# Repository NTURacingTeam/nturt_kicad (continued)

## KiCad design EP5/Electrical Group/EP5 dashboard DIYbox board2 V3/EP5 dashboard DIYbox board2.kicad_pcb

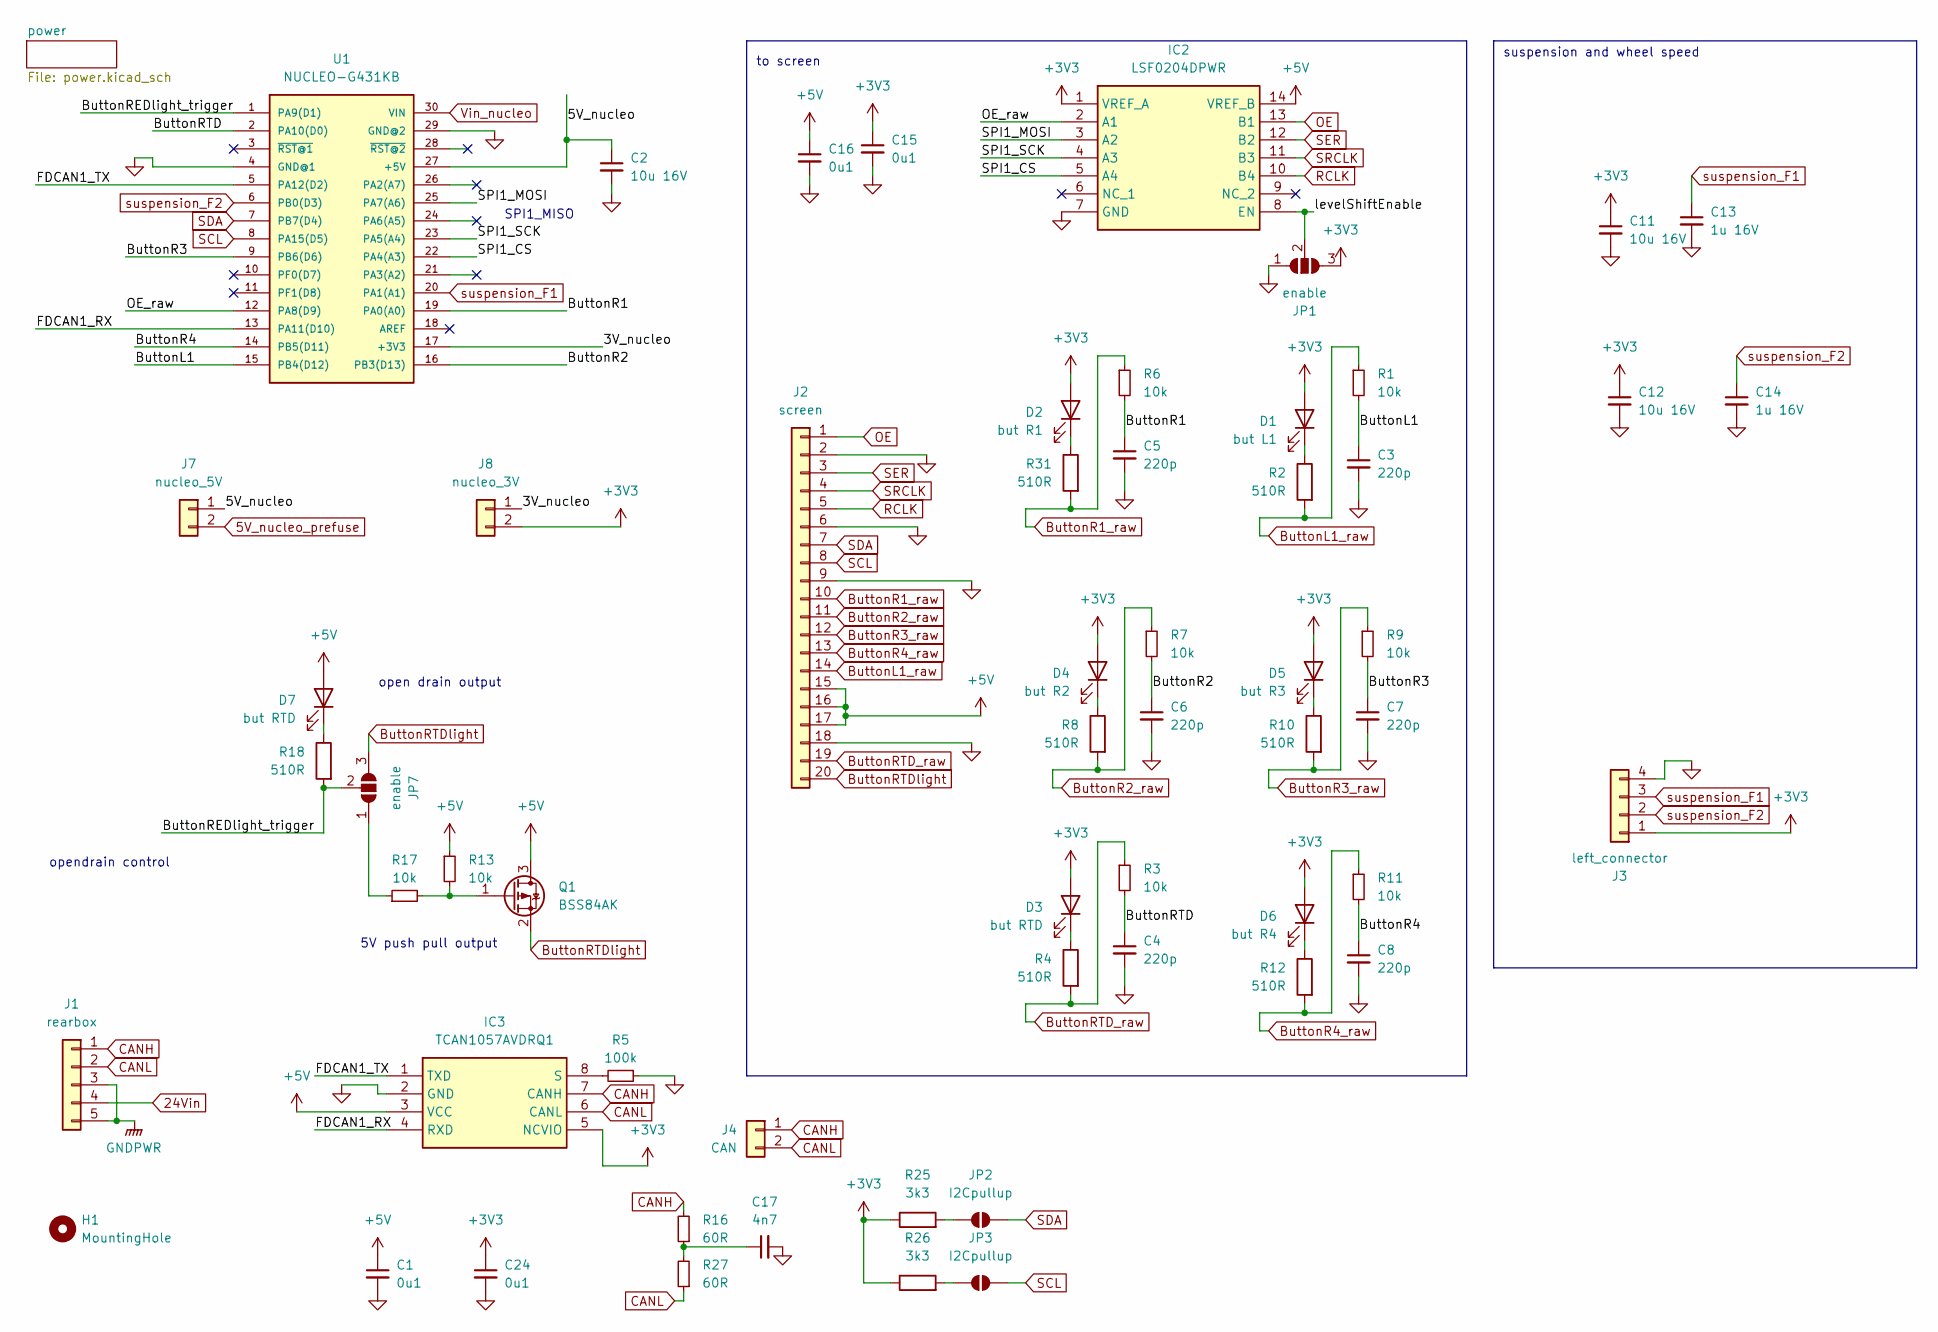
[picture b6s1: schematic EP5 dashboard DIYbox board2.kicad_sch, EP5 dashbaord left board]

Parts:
C1, C15, C16, C24: 0u1; C_0603_1608Metric
C2, C11, C12: 10u 16V; C_0805_2012Metric
C3, C4, C5, C6, C7, C8: 220p; C_0603_1608Metric
C13, C14: 1u 16V; C_0603_1608Metric
C17: 4n7; C_0603_1608Metric
D1: but L1; LED_0603_1608Metric
D2: but R1; LED_0603_1608Metric
D3, D7: but RTD; LED_0603_1608Metric
D4: but R2; LED_0603_1608Metric
D5: but R3; LED_0603_1608Metric
D6: but R4; LED_0603_1608Metric
H1: MountingHole; MountingHole_4.3mm_M4
IC2: LSF0204DPWR; SOP65P640X120-14N; Mouser Part Number 595-LSF0204DPWR
IC3: TCAN1057AVDRQ1; SOIC127P600X175-8N; Mouser Part Number 595-TCAN1057AVDRQ1
J1: rearbox; WP-04F3-26-11
J2: screen; IDC-Header_2x10_P2.54mm_Vertical
J3: left_connector; JST_XH_S4B-XH-A_1x04_P2.50mm_Horizontal
J4: CAN; PinHeader_1x02_P2.54mm_Vertical
J7: nucleo_5V; PinHeader_1x02_P2.54mm_Vertical
J8: nucleo_3V; PinHeader_1x02_P2.54mm_Vertical
JP1, JP7: enable; SolderJumper-3_P1.3mm_Open_RoundedPad1.0x1.5mm_NumberLabels
JP2, JP3: I2Cpullup; SolderJumper-2_P1.3mm_Open_RoundedPad1.0x1.5mm
Q1: BSS84AK; SOT-23-3
R1, R3, R6, R7, R9, R11, R13, R17: 10k; R_0603_1608Metric
R2, R4, R8, R10, R12, R18, R31: 510R; R_0603_1608Metric
R5: 100k; R_0603_1608Metric
R16, R27: 60R; R_0603_1608Metric
R25, R26: 3k3; R_0603_1608Metric_Pad0.98x0.95mm_HandSolder
U1: NUCLEO-G431KB; MANUFACTURER_PART_NUMBER NUCLEO-F303K8

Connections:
5V_nucleo_prefuse: J7.2; also elsewhere on the board
24Vin: J1.4; also elsewhere on the board
+3V3: C11.1, C12.1, C15.1, C24.1, D1.2 (A), D2.2 (A), D3.2 (A), D4.2 (A), D5.2 (A), D6.2 (A), IC2.1 (VREF_A), IC3.5 (NCVIO), J3.1, J8.2, JP1.3 (B), R25.1, R26.1; also elsewhere on the board
+5V: C1.1, C16.1, D7.2 (A), IC2.14 (VREF_B), IC3.3 (VCC), J2.15, J2.16, J2.17, Q1.3 (D), R13.1; also elsewhere on the board
/3V_nucleo: J8.1, U1.17 (+3V3)
/5V_nucleo: C2.1, J7.1, U1.27 (+5V)
/ButtonL1: C3.1, R1.2, U1.15 (PB4(D12))
/ButtonR1: C5.1, R6.2, U1.19 (PA0(A0))
/ButtonR2: C6.1, R7.2, U1.16 (PB3(D13))
/ButtonR3: C7.1, R9.2, U1.9 (PB6(D6))
/ButtonR4: C8.1, R11.2, U1.14 (PB5(D11))
/ButtonREDlight_trigger: JP7.2 (C), R18.2, U1.1 (PA9(D1))
/ButtonRTD: C4.1, R3.2, U1.2 (PA10(D0))
/FDCAN1_RX: IC3.4 (RXD), U1.13 (PA11(D10))
/FDCAN1_TX: IC3.1 (TXD), U1.5 (PA12(D2))
/OE_raw: IC2.2 (A1), U1.12 (PA8(D9))
/SPI1_CS: IC2.5 (A4), U1.22 (PA4(A3))
/SPI1_MOSI: IC2.3 (A2), U1.25 (PA7(A6))
/SPI1_SCK: IC2.4 (A3), U1.23 (PA5(A4))
/levelShiftEnable: IC2.8 (EN), JP1.2 (C)
ButtonL1_raw: J2.14, R1.1, R2.2
ButtonR1_raw: J2.10, R6.1, R31.2
ButtonR2_raw: J2.11, R7.1, R8.2
ButtonR3_raw: J2.12, R9.1, R10.2
ButtonR4_raw: J2.13, R11.1, R12.2
ButtonRTD_raw: J2.19, R3.1, R4.2
ButtonRTDlight: J2.20, JP7.3 (B), Q1.2 (S)
CANH: IC3.7 (CANH), J1.1, J4.1, R16.2
CANL: IC3.6 (CANL), J1.2, J4.2, R27.1
GND: C1.2, C2.2, C3.2, C4.2, C5.2, C6.2, C7.2, C8.2, C11.2, C12.2, C13.2, C14.2, C15.2, C16.2, C17.2, C24.2, IC2.7 (GND), IC3.2 (GND), J2.2, J2.6, J2.9, J2.18, J3.4, JP1.1 (A), R5.1, U1.4 (GND@1), U1.29 (GND@2); also elsewhere on the board
GNDPWR: J1.3, J1.5; also elsewhere on the board
unnamed: C17.1, R16.1, R27.2
unnamed: D1.1 (K), R2.1
unnamed: D2.1 (K), R31.1
unnamed: D3.1 (K), R4.1
unnamed: D4.1 (K), R8.1
unnamed: D5.1 (K), R10.1
unnamed: D6.1 (K), R12.1
unnamed: D7.1 (K), R18.1
unnamed: IC3.8 (S), R5.2
unnamed: JP2.1 (A), R25.2
unnamed: JP3.1 (A), R26.2
unnamed: JP7.1 (A), R17.1
unnamed: Q1.1 (G), R13.2, R17.2
OE: IC2.13 (B1), J2.1
RCLK: IC2.10 (B4), J2.5
SCL: J2.8, JP3.2 (B), U1.8 (PA15(D5))
SDA: J2.7, JP2.2 (B), U1.7 (PB7(D4))
SER: IC2.12 (B2), J2.3
SRCLK: IC2.11 (B3), J2.4
Vin_nucleo: U1.30 (VIN); also elsewhere on the board
suspension_F1: C13.1, J3.3, U1.20 (PA1(A1))
suspension_F2: C14.1, J3.2, U1.6 (PB0(D3))

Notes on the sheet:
5V push pull output
opendrain control
to screen
SPI1_MISO
suspension and wheel speed
open drain output

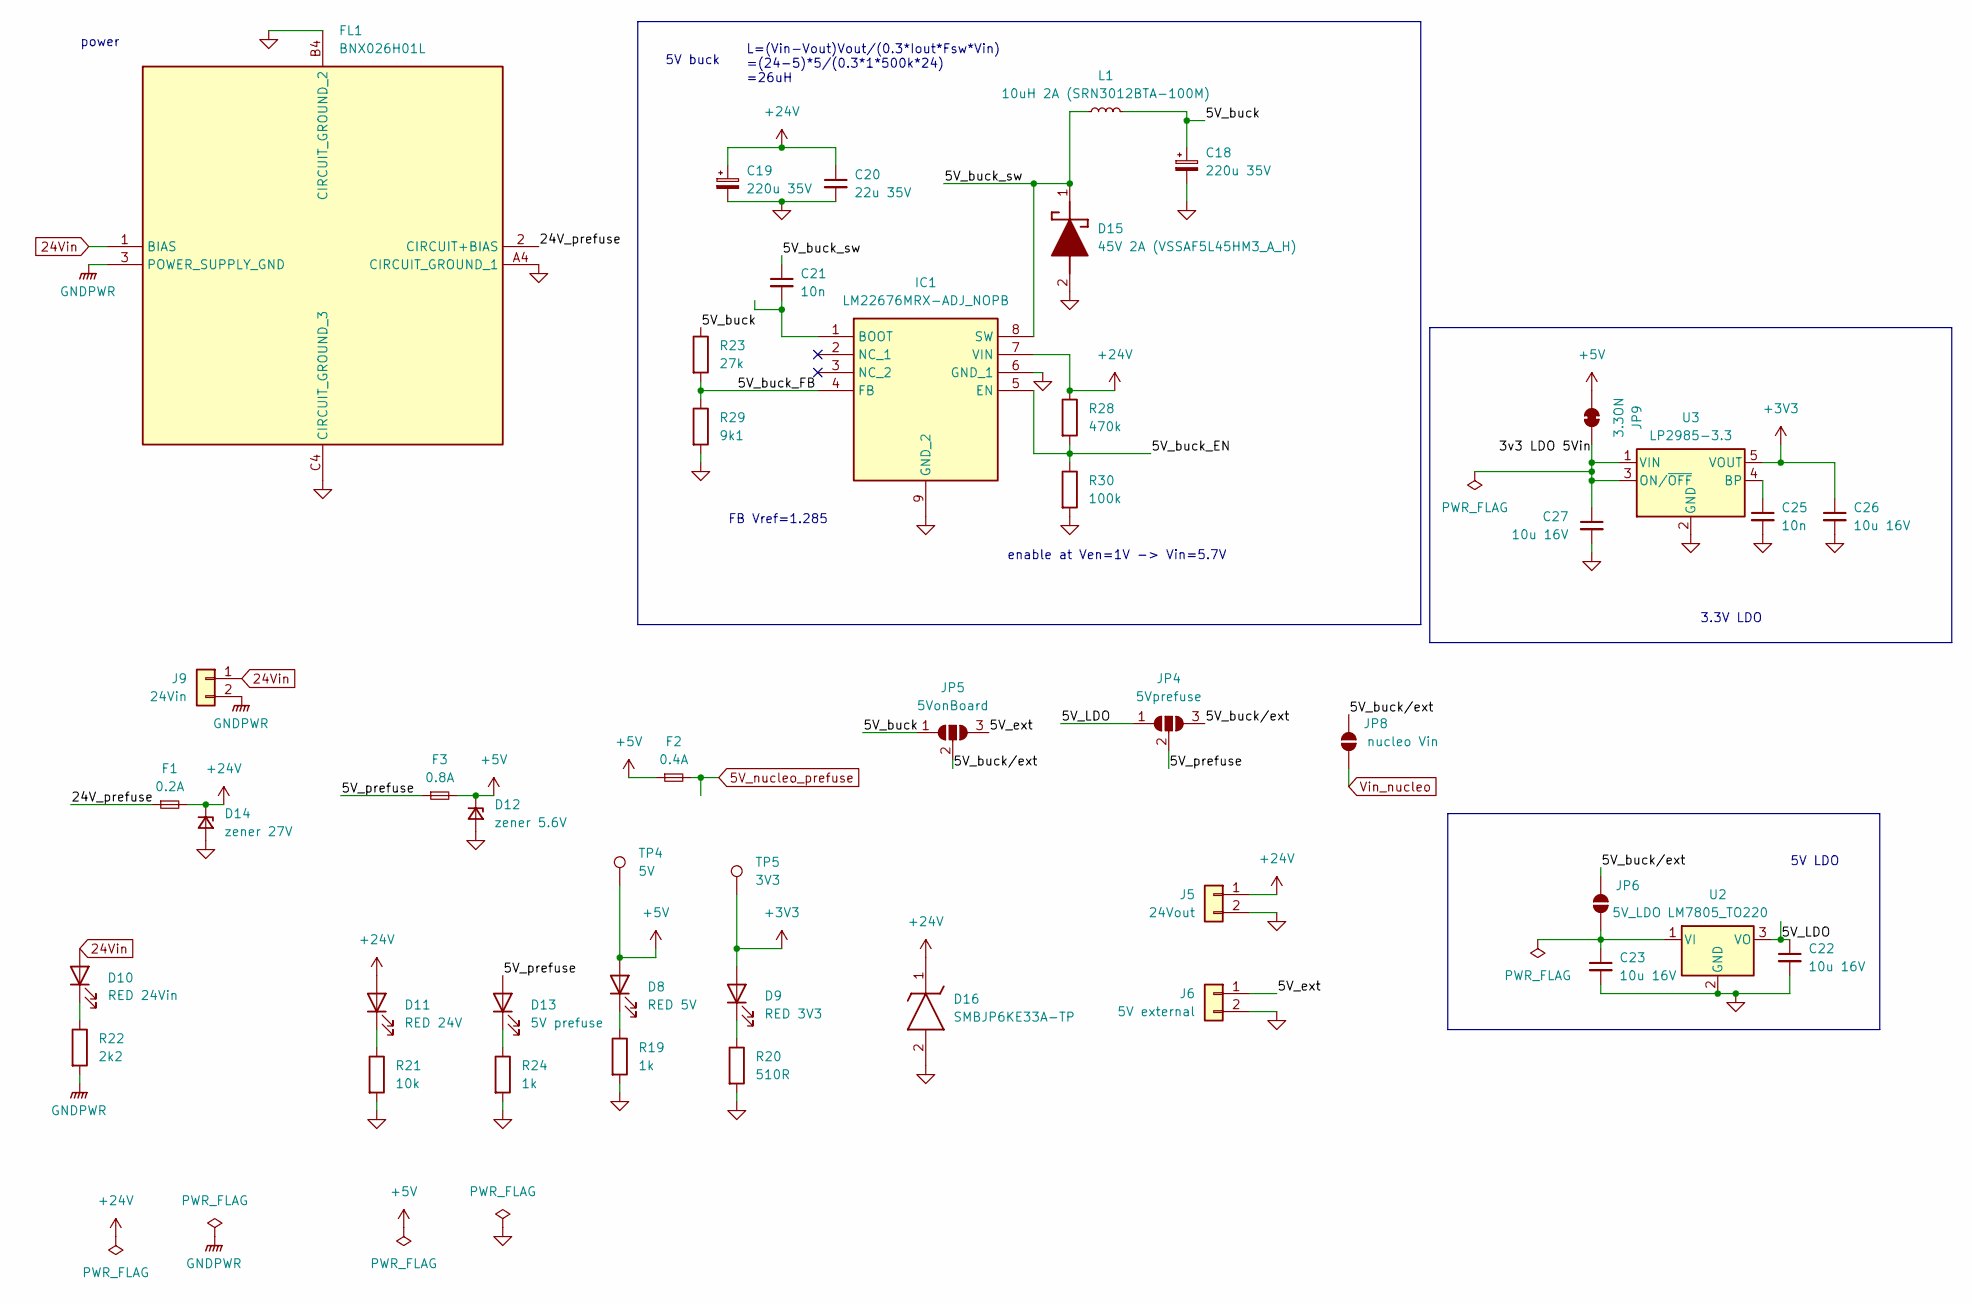
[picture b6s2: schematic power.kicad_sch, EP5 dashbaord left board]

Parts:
C18, C19: 220u 35V; CP_Radial_D8.0mm_P3.80mm
C20: 22u 35V; C_1206_3216Metric
C21, C25: 10n; C_0603_1608Metric
C22, C23, C26, C27: 10u 16V; C_0805_2012Metric
D8: RED 5V; LED_0603_1608Metric
D9: RED 3V3; LED_0603_1608Metric
D10: RED 24Vin; LED_0603_1608Metric
D11: RED 24V; LED_0603_1608Metric
D12: zener 5.6V; D_MiniMELF
D13: 5V prefuse; LED_0603_1608Metric
D14: zener 27V; D_MiniMELF
D15: 45V 2A (VSSAF5L45HM3_A_H); SODFL5226X100N; Mouser Part Number 78-VSSAF5L45HM3_A/H
D16: SMBJP6KE33A-TP; DIOM5336X262N; Mouser Part Number 833-SMBJP6KE33A-TP
F1: 0.2A; Fuse_2512_6332Metric_Pad1.52x3.35mm_HandSolder
F2: 0.4A; Fuse_2512_6332Metric_Pad1.52x3.35mm_HandSolder
F3: 0.8A; Fuse_2512_6332Metric_Pad1.52x3.35mm_HandSolder
FL1: BNX026H01L; BNX024H01K; Mouser Part Number 81-BNX026H01L
IC1: LM22676MRX-ADJ_NOPB; SOIC127P600X170-9N; Mouser Part Number 926-LM22676MRXADJNPB
J5: 24Vout; PinHeader_1x02_P2.54mm_Vertical
J6: 5V external; JST_XH_B2B-XH-A_1x02_P2.50mm_Vertical
J9: 24Vin; JST_XH_B2B-XH-A_1x02_P2.50mm_Vertical
JP4: 5Vprefuse; SolderJumper-3_P1.3mm_Open_Pad1.0x1.5mm_NumberLabels
JP5: 5VonBoard; SolderJumper-3_P1.3mm_Open_Pad1.0x1.5mm_NumberLabels
JP6: 5V_LDO; SolderJumper-2_P1.3mm_Open_Pad1.0x1.5mm
JP8: nucleo Vin; SolderJumper-2_P1.3mm_Open_Pad1.0x1.5mm
JP9: 3.3ON; SolderJumper-2_P1.3mm_Open_Pad1.0x1.5mm
L1: 10uH 2A (SRN3012BTA-100M); SRN3012BTA100M
R19, R24: 1k; R_0603_1608Metric
R20: 510R; R_0603_1608Metric
R21: 10k; R_0603_1608Metric
R22: 2k2; R_0603_1608Metric
R23: 27k; R_0603_1608Metric
R28: 470k; R_0603_1608Metric
R29: 9k1; R_0603_1608Metric
R30: 100k; R_0603_1608Metric
TP4: 5V; TestPoint_Pad_D1.0mm
TP5: 3V3; TestPoint_Pad_D1.0mm
U2: LM7805_TO220; TO-220-3_Vertical
U3: LP2985-3.3; SOT-23-5

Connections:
5V_nucleo_prefuse: F2.2; also elsewhere on the board
24Vin: D10.2 (A), FL1.1 (BIAS), J9.1; also elsewhere on the board
+3V3: C26.1, D9.2 (A), TP5.1, U3.5 (VOUT); also elsewhere on the board
+5V: D8.2 (A), D12.1 (K), F2.1, F3.2, JP9.1 (A), TP4.1; also elsewhere on the board
+24V: C19.1, C20.1, D11.2 (A), D14.1 (K), D16.1 (K), F1.2, IC1.7 (VIN), J5.1, R28.1
/power/3v3 LDO 5Vin: C27.1, JP9.2 (B), U3.1 (VIN), U3.3 (ON/~OFF)
/power/5V_LDO: C22.1, JP4.1 (A), U2.3 (VO)
/power/5V_buck: C18.1, JP5.1 (A), L1.2, R23.1
/power/5V_buck_EN: IC1.5 (EN), R28.2, R30.1
/power/5V_buck_FB: IC1.4 (FB), R23.2, R29.1
/power/5V_buck_sw: C21.1, D15.1 (K), IC1.8 (SW), L1.1
/power/5V_buck/ext: JP4.3 (B), JP5.2 (C), JP6.1 (A), JP8.1 (A)
/power/5V_ext: J6.1, JP5.3 (B)
/power/5V_prefuse: D13.2 (A), F3.1, JP4.2 (C)
/power/24V_prefuse: F1.1, FL1.2 (CIRCUIT+BIAS)
GND: C18.2, C19.2, C20.2, C22.2, C23.2, C25.2, C26.2, C27.2, D12.2 (A), D14.2 (A), D15.2 (A), D16.2 (A), FL1.A4 (CIRCUIT_GROUND_1), FL1.B4 (CIRCUIT_GROUND_2), FL1.C4 (CIRCUIT_GROUND_3), IC1.6 (GND_1), IC1.9 (GND_2), J5.2, J6.2, R19.2, R20.2, R21.2, R24.2, R29.2, R30.2, U2.2 (GND), U3.2 (GND); also elsewhere on the board
GNDPWR: FL1.3 (POWER_SUPPLY_GND), J9.2, R22.2; also elsewhere on the board
unnamed: D8.1 (K), R19.1
unnamed: D9.1 (K), R20.1
unnamed: D10.1 (K), R22.1
unnamed: D11.1 (K), R21.1
unnamed: D13.1 (K), R24.1
unnamed: C21.2, IC1.1 (BOOT)
unnamed: C23.1, JP6.2 (B), U2.1 (VI)
unnamed: C25.1, U3.4 (BP)
Vin_nucleo: JP8.2 (B); also elsewhere on the board

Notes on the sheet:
L=(Vin-Vout)Vout/(0.3*Iout*Fsw*Vin) =(24-5)*5/(0.3*1*500k*24) =26uH
enable at Ven=1V -> Vin=5.7V
5V LDO
5V buck
3.3V LDO
power
FB Vref=1.285

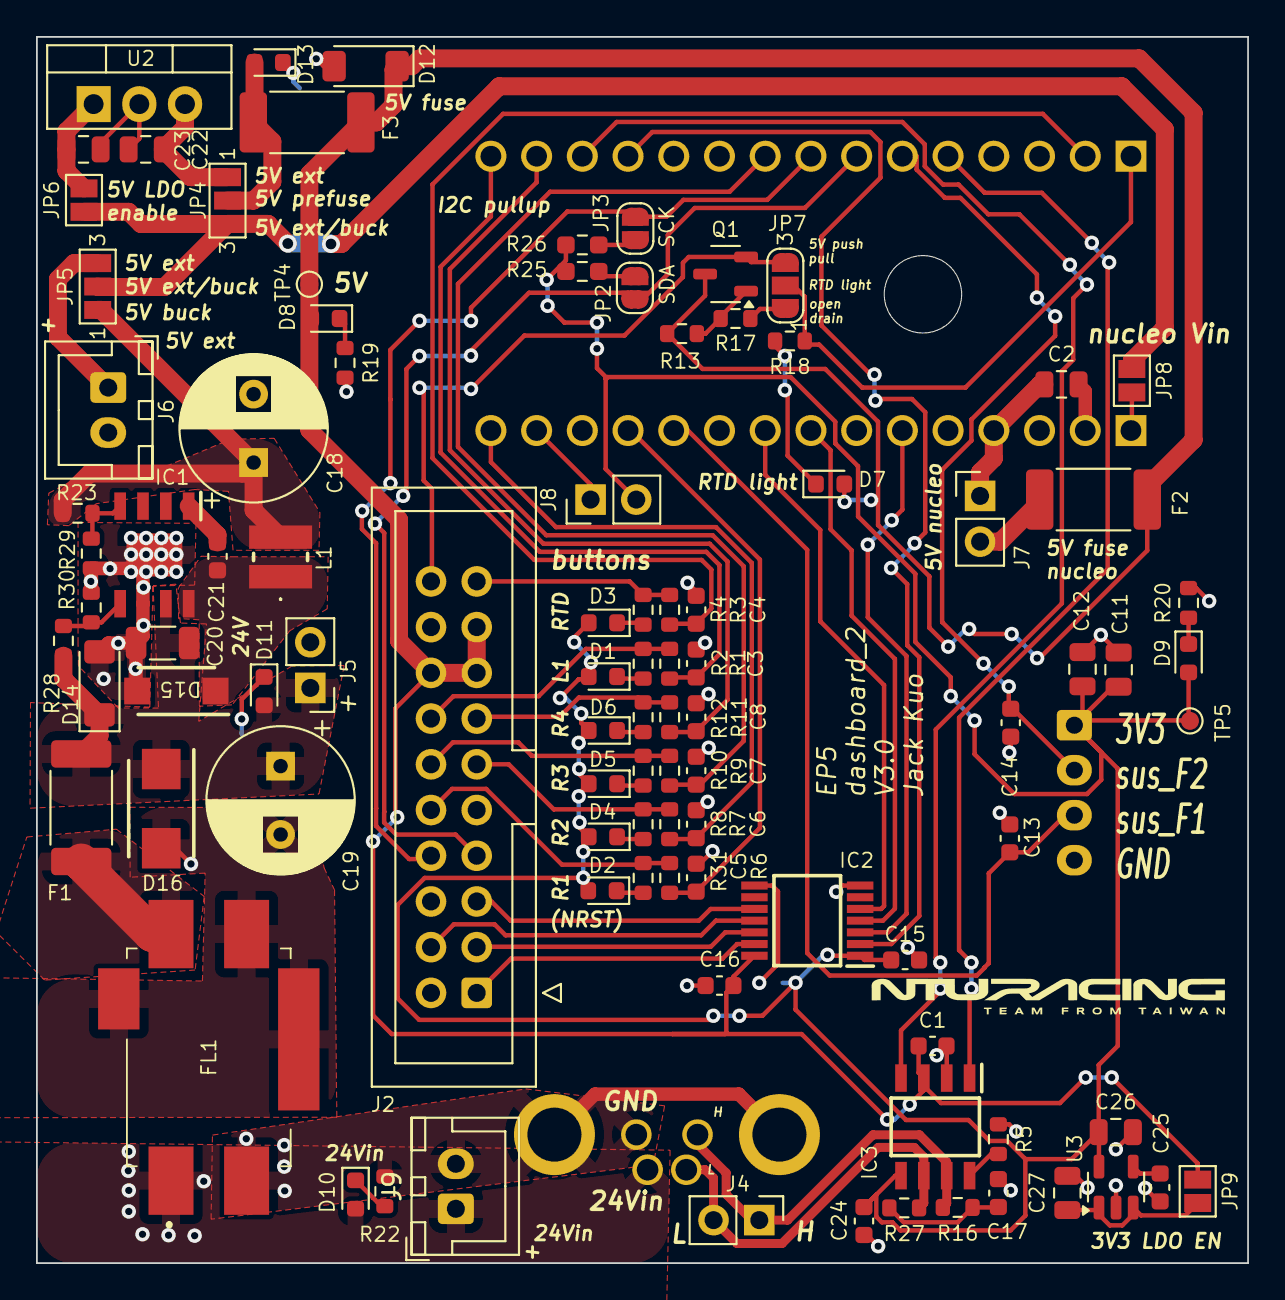
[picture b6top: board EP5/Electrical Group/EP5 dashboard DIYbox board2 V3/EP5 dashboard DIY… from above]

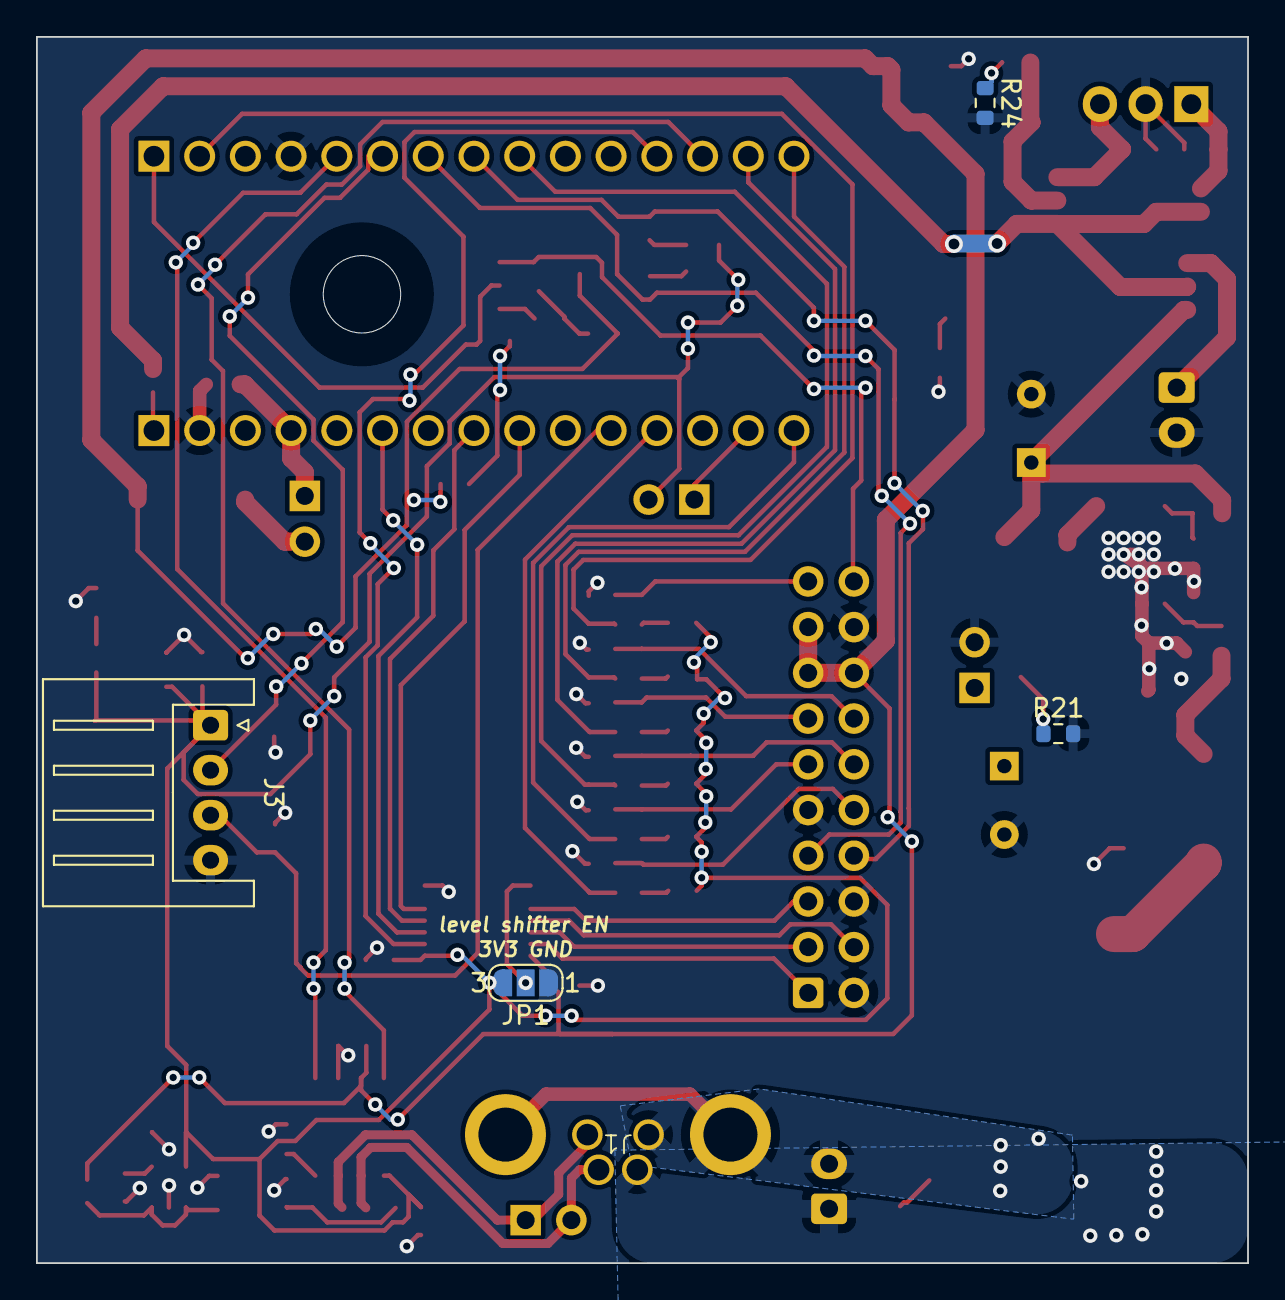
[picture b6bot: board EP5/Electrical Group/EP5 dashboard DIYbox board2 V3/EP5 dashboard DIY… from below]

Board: 2 copper layers, 67.3 x 68.1 mm, 103 parts (5 on the bottom side), 72 nets.

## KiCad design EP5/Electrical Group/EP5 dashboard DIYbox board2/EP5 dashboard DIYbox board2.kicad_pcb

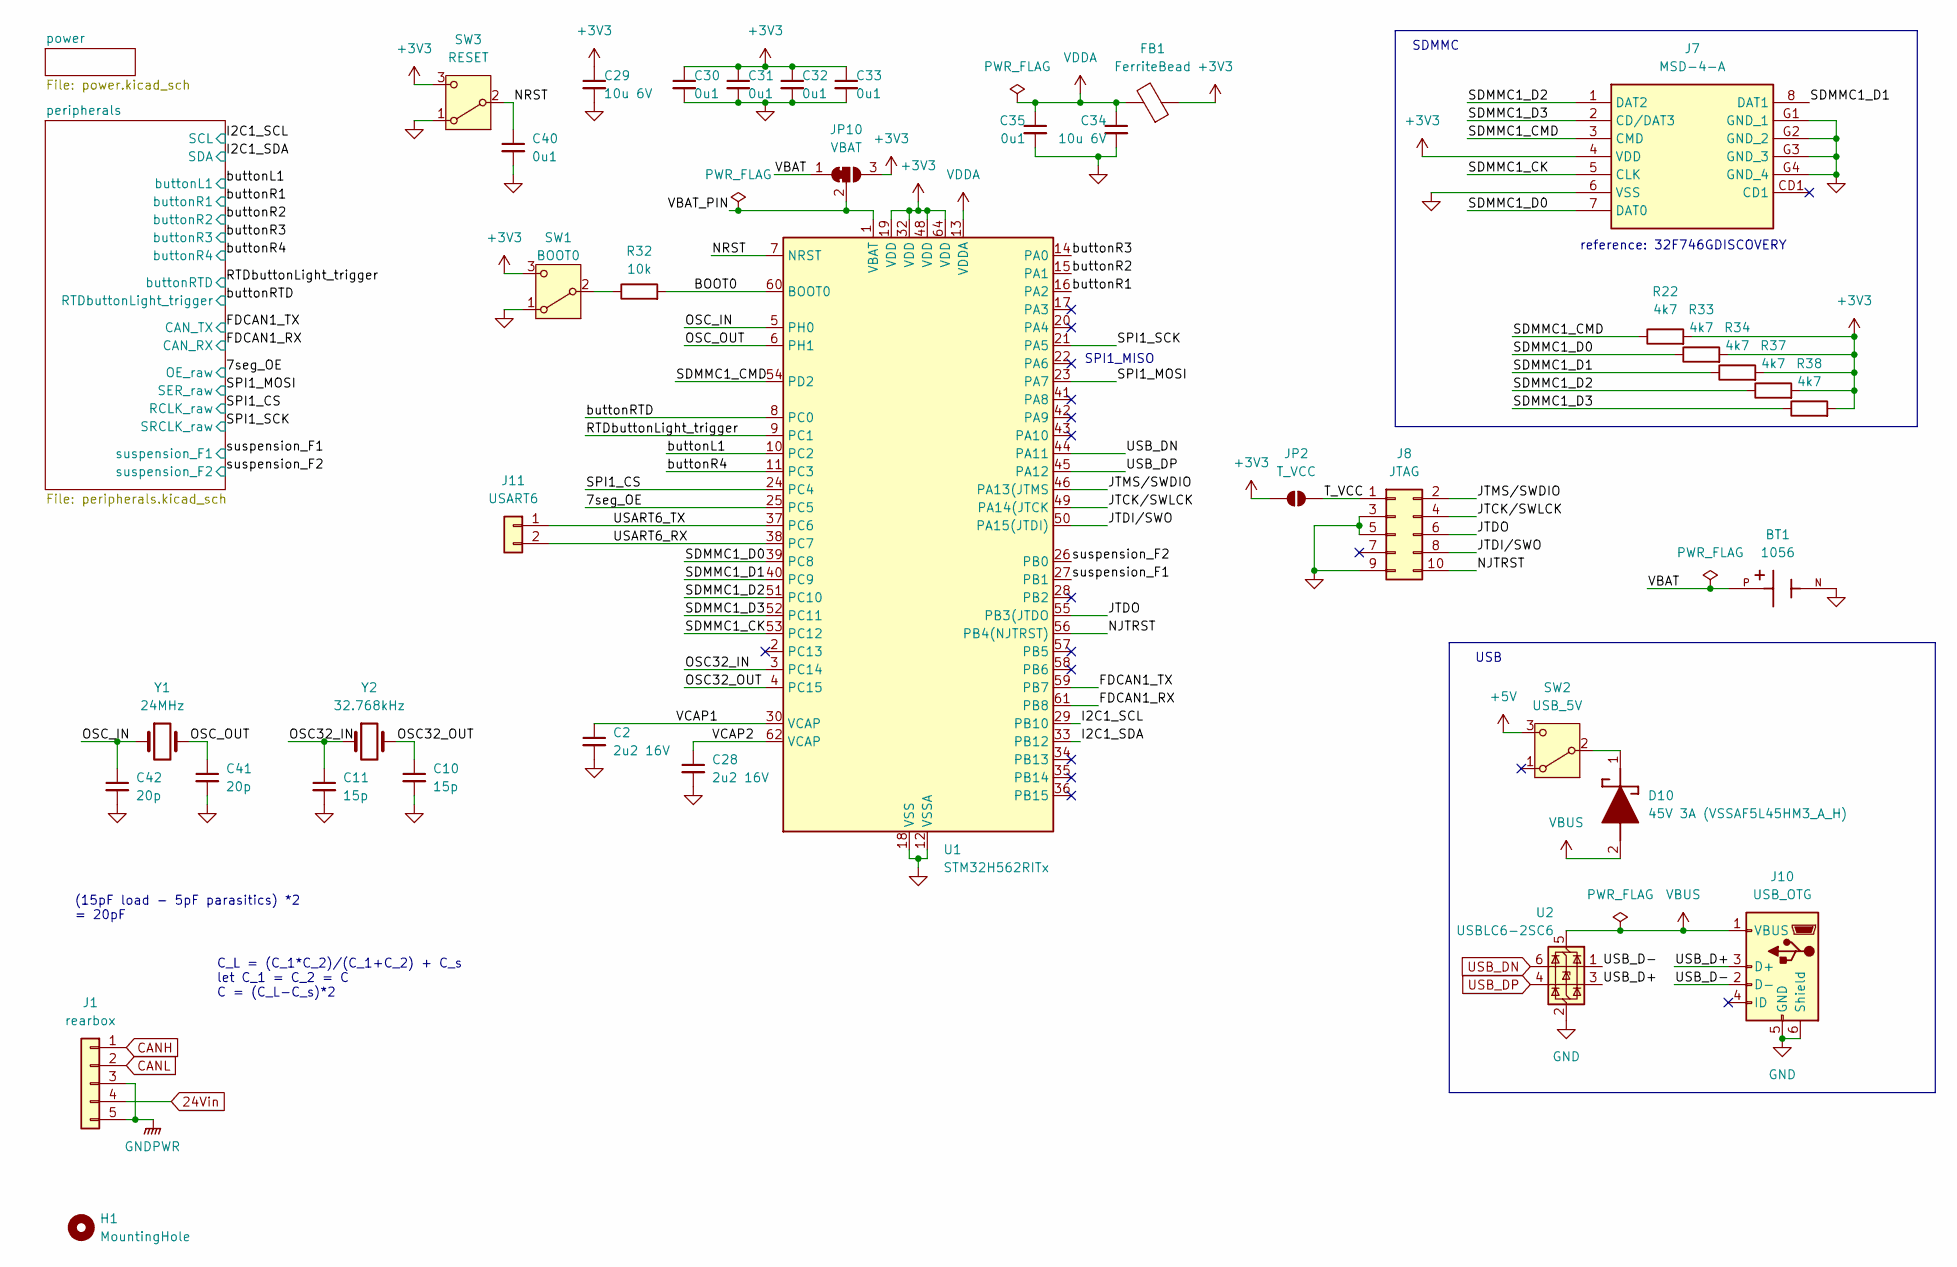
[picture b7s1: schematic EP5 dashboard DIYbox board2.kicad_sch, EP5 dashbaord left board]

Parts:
BT1: 1056; BAT_1056; PARTREV D
C2, C28: 2u2 16V; C_0603_1608Metric
C10, C11: 15p; C_0603_1608Metric
C29, C34: 10u 6V; C_0603_1608Metric
C30, C31, C32, C33, C35, C40: 0u1; C_0603_1608Metric
C41, C42: 20p; C_0603_1608Metric
D10: 45V 3A (VSSAF5L45HM3_A_H); SODFL5226X100N; Mouser Part Number 78-VSSAF5L45HM3_A/H
FB1: FerriteBead; L_0805_2012Metric
H1: MountingHole; MountingHole_4.3mm_M4
J1: rearbox; WP-04F3-26-11
J7: MSD-4-A; MSD4A; Mouser Part Number 179-MSD-4-A
J8: JTAG; IDC-Header_2x05_P2.00mm_Vertical
J10: USB_OTG; USB_Micro-B_Wuerth_629105150521
J11: USART6; PinHeader_1x02_P2.54mm_Vertical
JP2: T_VCC; SolderJumper-2_P1.3mm_Open_RoundedPad1.0x1.5mm
JP10: VBAT; SolderJumper-3_P1.3mm_Open_RoundedPad1.0x1.5mm
R22, R33, R34, R37, R38: 4k7; R_0603_1608Metric
R32: 10k; R_0603_1608Metric
SW1: BOOT0; PinHeader_1x03_P2.54mm_Vertical
SW2: USB_5V; PinHeader_1x03_P2.54mm_Vertical
SW3: RESET; PinHeader_1x03_P2.54mm_Vertical
U1: STM32H562RITx; LQFP-64_10x10mm_P0.5mm
U2: USBLC6-2SC6; SOT-23-6
Y1: 24MHz; Crystal_C38-LF_D3.0mm_L8.0mm_Vertical
Y2: 32.768kHz; Crystal_C38-LF_D3.0mm_L8.0mm_Vertical

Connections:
24Vin: J1.4; also elsewhere on the board
+3V3: C29.1, C30.1, C31.1, C32.1, C33.1, FB1.1, J7.4 (VDD), JP2.1 (A), JP10.3 (B), R22.2, R33.2, R34.2, R37.2, R38.2, SW1.3 (C), SW3.3 (C), U1.19 (VDD), U1.32 (VDD), U1.48 (VDD), U1.64 (VDD); also elsewhere on the board
+5V: SW2.3 (C); also elsewhere on the board
/7seg_OE: U1.25 (PC5); also elsewhere on the board
/BOOT0: R32.2, U1.60 (BOOT0)
/FDCAN1_RX: U1.61 (PB8); also elsewhere on the board
/FDCAN1_TX: U1.59 (PB7); also elsewhere on the board
/I2C1_SCL: U1.29 (PB10); also elsewhere on the board
/I2C1_SDA: U1.33 (PB12); also elsewhere on the board
/JTCK/SWLCK: J8.4, U1.49 (PA14(JTCK)
/JTDI/SWO: J8.8, U1.50 (PA15(JTDI))
/JTDO: J8.6, U1.55 (PB3(JTDO)
/JTMS/SWDIO: J8.2, U1.46 (PA13(JTMS)
/NJTRST: J8.10, U1.56 (PB4(NJTRST))
/NRST: C40.1, SW3.2 (B), U1.7 (NRST)
/OSC32_IN: C11.1, U1.3 (PC14), Y2.1
/OSC32_OUT: C10.1, U1.4 (PC15), Y2.2
/OSC_IN: C42.1, U1.5 (PH0), Y1.1
/OSC_OUT: C41.1, U1.6 (PH1), Y1.2
/RTDbuttonLight_trigger: U1.9 (PC1); also elsewhere on the board
/SDMMC1_CK: J7.5 (CLK), U1.53 (PC12)
/SDMMC1_CMD: J7.3 (CMD), R22.1, U1.54 (PD2)
/SDMMC1_D0: J7.7 (DAT0), R33.1, U1.39 (PC8)
/SDMMC1_D1: J7.8 (DAT1), R34.1, U1.40 (PC9)
/SDMMC1_D2: J7.1 (DAT2), R37.1, U1.51 (PC10)
/SDMMC1_D3: J7.2 (CD/DAT3), R38.1, U1.52 (PC11)
/SPI1_CS: U1.24 (PC4); also elsewhere on the board
/SPI1_MOSI: U1.23 (PA7); also elsewhere on the board
/SPI1_SCK: U1.21 (PA5); also elsewhere on the board
/T_VCC: J8.1, JP2.2 (B)
/USART6_RX: J11.2, U1.38 (PC7)
/USART6_TX: J11.1, U1.37 (PC6)
/USB_D+: J10.3 (D+), U2.3 (I/O2)
/USB_D-: J10.2 (D-), U2.1 (I/O1)
/VBAT: BT1.P, JP10.1 (A)
/VBAT_PIN: JP10.2 (C), U1.1 (VBAT)
/VCAP1: C2.1, U1.30 (VCAP)
/VCAP2: C28.1, U1.62 (VCAP)
/buttonL1: U1.10 (PC2); also elsewhere on the board
/buttonR1: U1.16 (PA2); also elsewhere on the board
/buttonR2: U1.15 (PA1); also elsewhere on the board
/buttonR3: U1.14 (PA0); also elsewhere on the board
/buttonR4: U1.11 (PC3); also elsewhere on the board
/buttonRTD: U1.8 (PC0); also elsewhere on the board
/suspension_F1: U1.27 (PB1); also elsewhere on the board
/suspension_F2: U1.26 (PB0); also elsewhere on the board
CANH: J1.1; also elsewhere on the board
CANL: J1.2; also elsewhere on the board
GND: BT1.N, C2.2, C10.2, C11.2, C28.2, C29.2, C30.2, C31.2, C32.2, C33.2, C34.2, C35.2, C40.2, C41.2, C42.2, J7.6 (VSS), J7.G1 (GND_1), J7.G2 (GND_2), J7.G3 (GND_3), J7.G4 (GND_4), J8.3, J8.5, J8.9, J10.5 (GND), J10.6 (Shield), SW1.1 (A), SW3.1 (A), U1.12 (VSSA), U1.18 (VSS), U1.31 (VSS), U1.47 (VSS), U1.63 (VSS), U2.2 (GND); also elsewhere on the board
GNDPWR: J1.3, J1.5; also elsewhere on the board
unnamed: D10.1 (K), SW2.2 (B)
unnamed: R32.1, SW1.2 (B)
USB_DN: U1.44 (PA11), U2.6 (I/O1)
USB_DP: U1.45 (PA12), U2.4 (I/O2)
VBUS: D10.2 (A), J10.1 (VBUS), U2.5 (VBUS)
VDDA: C34.1, C35.1, FB1.2, U1.13 (VDDA)

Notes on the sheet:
USB
reference: 32F746GDISCOVERY
(15pF load - 5pF parasitics) *2 = 20pF
C_L = (C_1*C_2)/(C_1+C_2) + C_s let C_1 = C_2 = C C = (C_L-C_s)*2
SDMMC
SPI1_MISO

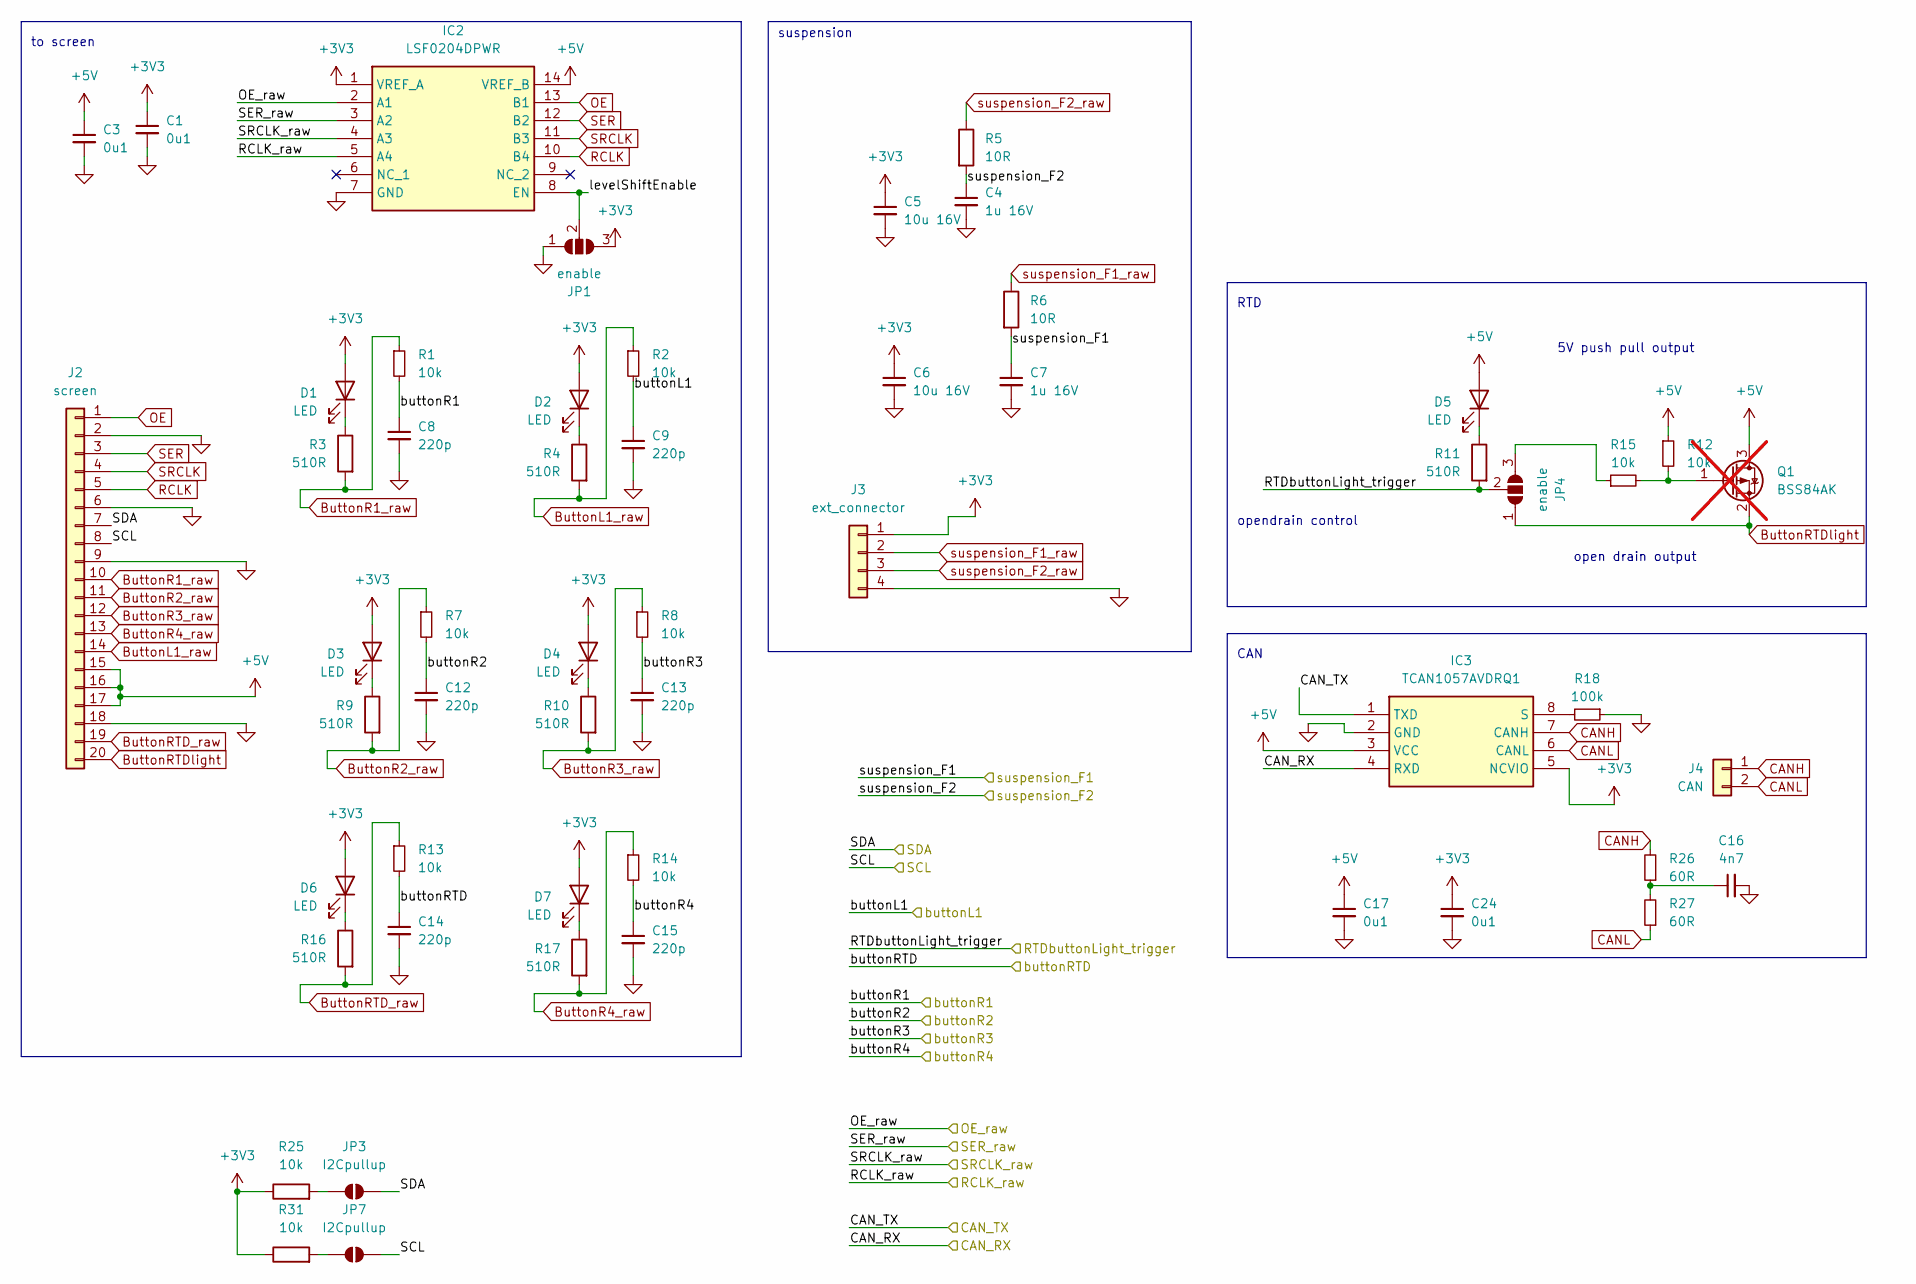
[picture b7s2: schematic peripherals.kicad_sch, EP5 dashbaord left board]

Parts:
C1, C3, C17, C24: 0u1; C_0603_1608Metric
C4, C7: 1u 16V; C_0603_1608Metric
C5, C6: 10u 16V; C_0805_2012Metric
C8, C9, C12, C13, C14, C15: 220p; C_0603_1608Metric
C16: 4n7; C_0603_1608Metric
D1, D2, D3, D4, D5, D6, D7: LED; LED_0603_1608Metric
IC2: LSF0204DPWR; SOP65P640X120-14N; Mouser Part Number 595-LSF0204DPWR
IC3: TCAN1057AVDRQ1; SOIC127P600X175-8N; Mouser Part Number 595-TCAN1057AVDRQ1
J2: screen; IDC-Header_2x10_P2.54mm_Vertical
J3: ext_connector; JST_XH_S4B-XH-A_1x04_P2.50mm_Horizontal
J4: CAN; PinHeader_1x02_P2.54mm_Vertical
JP1: enable; SolderJumper-3_P1.3mm_Open_Pad1.0x1.5mm
JP3, JP7: I2Cpullup; SolderJumper-2_P1.3mm_Open_RoundedPad1.0x1.5mm
JP4: enable; SolderJumper-3_P1.3mm_Open_RoundedPad1.0x1.5mm
Q1: BSS84AK; SOT-23-3; not fitted
R1, R2, R7, R8, R12, R13, R14, R15, R25, R31: 10k; R_0603_1608Metric
R3, R4, R9, R10, R11, R16, R17: 510R; R_0603_1608Metric
R5, R6: 10R; R_0603_1608Metric
R18: 100k; R_0603_1608Metric
R26, R27: 60R; R_0603_1608Metric

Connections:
+3V3: C1.1, C5.1, C6.1, C24.1, D1.2 (A), D2.2 (A), D3.2 (A), D4.2 (A), D6.2 (A), D7.2 (A), IC2.1 (VREF_A), IC3.5 (NCVIO), J3.1, JP1.3 (B), R25.1, R31.1; also elsewhere on the board
+5V: C3.1, C17.1, D5.2 (A), IC2.14 (VREF_B), IC3.3 (VCC), J2.15, J2.16, J2.17, Q1.3 (D), R12.1; also elsewhere on the board
/7seg_OE: IC2.2 (A1); also elsewhere on the board
/FDCAN1_RX: IC3.4 (RXD); also elsewhere on the board
/FDCAN1_TX: IC3.1 (TXD); also elsewhere on the board
/I2C1_SCL: J2.8, JP7.2 (B); also elsewhere on the board
/I2C1_SDA: J2.7, JP3.2 (B); also elsewhere on the board
/RTDbuttonLight_trigger: C14.1, R13.2; also elsewhere on the board
/SPI1_CS: IC2.5 (A4); also elsewhere on the board
/SPI1_MOSI: IC2.3 (A2); also elsewhere on the board
/SPI1_SCK: IC2.4 (A3); also elsewhere on the board
/buttonL1: C9.1, R2.2; also elsewhere on the board
/buttonR1: C8.1, R1.2; also elsewhere on the board
/buttonR2: C12.1, R7.2; also elsewhere on the board
/buttonR3: C13.1, R8.2; also elsewhere on the board
/buttonR4: C15.1, R14.2; also elsewhere on the board
/buttonRTD: JP4.2 (C), R11.2; also elsewhere on the board
/peripherals/levelShiftEnable: IC2.8 (EN), JP1.2 (C)
/suspension_F1: C7.1, R6.2; also elsewhere on the board
/suspension_F2: C4.1, R5.2; also elsewhere on the board
ButtonL1_raw: J2.14, R2.1, R4.2
ButtonR1_raw: J2.10, R1.1, R3.2
ButtonR2_raw: J2.11, R7.1, R9.2
ButtonR3_raw: J2.12, R8.1, R10.2
ButtonR4_raw: J2.13, R14.1, R17.2
ButtonRTD_raw: J2.19, R13.1, R16.2
ButtonRTDlight: J2.20, JP4.1 (A), Q1.2 (S)
CANH: IC3.7 (CANH), J4.1, R26.2; also elsewhere on the board
CANL: IC3.6 (CANL), J4.2, R27.1; also elsewhere on the board
GND: C1.2, C3.2, C4.2, C5.2, C6.2, C7.2, C8.2, C9.2, C12.2, C13.2, C14.2, C15.2, C16.2, C17.2, C24.2, IC2.7 (GND), IC3.2 (GND), J2.2, J2.6, J2.9, J2.18, J3.4, JP1.1 (A), R18.1; also elsewhere on the board
unnamed: C16.1, R26.1, R27.2
unnamed: D1.1 (K), R3.1
unnamed: D2.1 (K), R4.1
unnamed: D3.1 (K), R9.1
unnamed: D4.1 (K), R10.1
unnamed: D5.1 (K), R11.1
unnamed: D6.1 (K), R16.1
unnamed: D7.1 (K), R17.1
unnamed: IC3.8 (S), R18.2
unnamed: JP3.1 (A), R25.2
unnamed: JP4.3 (B), R15.1
unnamed: JP7.1 (A), R31.2
unnamed: Q1.1 (G), R12.2, R15.2
OE: IC2.13 (B1), J2.1
RCLK: IC2.10 (B4), J2.5
SER: IC2.12 (B2), J2.3
SRCLK: IC2.11 (B3), J2.4
suspension_F1_raw: J3.2, R6.1
suspension_F2_raw: J3.3, R5.1

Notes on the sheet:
suspension
CAN
open drain output
opendrain control
to screen
5V push pull output
RTD
